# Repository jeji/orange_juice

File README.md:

# 我的频道 My Channel 
youtube: https://www.youtube.com/channel/UChTFW-Y9eg54AaTY_yama7A \
bilibili：https://b23.tv/pqzW2up

# 版本信息 Release Note
2022/10/09: v0.8 Reverse the polarity to match the common wire setup \
2022/02/06: v0.7 bate release version, passed function and stable test

**[香橙派Zero2版本](https://github.com/jeji/orange_juice_2)** \
**[Version for Orange Pi Zero2](https://github.com/jeji/orange_juice_2)** \

TODO:
- Integrate CAN controller/receivier
- Add motor driver socket as an universal socket for other feature, like: 
   - PWM controlled open loop buck convert for better fan noise 
   - Voron design MAX31865
   - Other SPI/UART/GPIO device

# 开始之前 Before You Start 
- 我并不是专业的电子工程师，设计本项目只是为了好玩和方便DIY Voron 3D打印机
- 你将自行承担由此带来的所有风险
- 社区有诸多反馈香橙派zero的CPU温度过高，所以在使用中请加强散热
- 本项目为基于GPL3.0的开源项目，欢迎魔改。如果你有更好的改进也请务必与我分享 
- **(!) 请特别注意文章中加粗和带"(!)"部分的内容**

- I'm not prefesstional electronic engineer, I designed this for fun and convenience while DIY my Voron printer
- You will take it as your own risk for any potential damages
- Overheat issue is being reported for OrangePi Zero H2+ CPU, hence a proper cooling fan even with cooling fin is strongly recommended
- This project is based GPL3.0 license, you are free to modify it to yourown version. Please do share the joy with me if you did that
- **(!) Please pay attention for the bold and with "(!)" content**

# 代号：橙汁 BoardName：Orange Juice

受全球芯片短缺情况影响，树莓派价格涨到了离谱的位置。
所以香橙派zero成了一个很好的替代品。120元左右的512MB版本可以满足做为klipper宿主的所有需求，甚至有点性能过剩。

klipper有诸多独特的功能需要使用到gpio针脚，每次都用排母端子去连接非常的不方便。在使用扩展板后不仅方便了许多，且可以得到额外的功能：
- 一个专为[ADXL345](https://www.adafruit.com/product/1231) 设计的接口将香橙派SPI1总线引出
- 一个专为[Adafruit MAX31865 board](https://www.adafruit.com/product/3328) 及其克隆版本设计的接口，作为软SPI使用了4个gpio接口
- 两个从香橙派引出的USB2.0 TypeA接口
- 一个UART接口
- 三组gpio控制的PWM输出接口，最大输出电压与输入电压相同
- 三组gpio接口配合5v电源接口，方便自定义其他功能
- 两组恒定5v输出接口
- 一个香橙派专用散热3010风扇安装位
- 自带降压电路，接受9~24V输入电压降压为5V供香橙派及其接口使用
- 扩展板大小及安装孔位与树莓派B系列保持一致
- 使用0805或更大尺寸封装贴片封装以方便手工贴片

Due to current chipset shortage sitatuion, raspberry pi price increase to an unreasonable level. 
Hence OrangePi Zero become a good alternative. A 25 dollars 512MB ram version meets all the requirments I need as a klipper host for my Voron V0.1, and actually even little bit over kill. 

Klipper has some advance features which need connect to gpio pins, it's not that convenience to use a pin header to connect gpio pin every time. Instead of that, with this board, it provides easier connection and more useful features:
- A dedicate [ADXL345](https://www.adafruit.com/product/1231) port is extended from OrangePi zero SPI1 bus
- A dedicate MAX31865 port connect to 4 gpio pins as a SW SPI connection, for [Adafruit MAX31865 board](https://www.adafruit.com/product/3328) or its clone
- Two USB2.0 Type A ports are extended from orange pi function pin
- A UART port for UART communication with printer MCU board
- Three klipper controllable pwm output ports, voltage depends on input DC voltage
- Three gpio port from orangepi with 5v power, for custom function
- Two 5v output ports
- A built-in 3010 chip cooling fan position
- A built-in step-down buck converter to convert DC 9~24v input to DC 5v to supply pi and 5v output socket
- Raspberry Pi B Serials board size and mount hole position compatible 
- 0805 or larger size SMD components are being used for hand soldering

# 如何使用 How to use
## 硬件 Hardware
PCB打板：[gerber文件](gerber/orange_juice_v0.8_gerber.zip)
- 你可以在嘉立创或者其他你喜欢的厂商免费打板
- 保持打板厂商默认设置即可

BOM：[电子元件BOM](bom/ibom.html)
- 在立创商城使用BOM单里lcsc part编号搜索即可找到对应原件型号
- 我使用的元件购买至淘宝，主要来自优信
- **(!) 香橙派针脚接头需要使用加高7.5mm的排母针脚，** 参考链接：[这里](https://item.taobao.com/item.htm?spm=a1z09.2.0.0.5abe2e8dp4SvIq&id=562698441144&_u=u181c59936e) 

PCB board：[gerber file](gerber/orange_juice_v0.8_gerber.zip)
- You can get the PCB board from JLC or other PCB manufactory 
- Usually, keep the defualt setting shall be ok when you place your order

BOM：[iBOM](bom/ibom.html)
- Search the component at [LCSC](https://lcsc.com/) via lcsc part number in the BOM
- I got my component from my trust taobao.com shop due to more reasble price 
- **(!) You need the famale pin head with 7.5mm extra feet height for orange pi,** reference link: [Here](https://item.taobao.com/item.htm?spm=a1z09.2.0.0.5abe2e8dp4SvIq&id=562698441144&_u=u181c59936e) 

## 软件 Software

请参考config目录下的orange_juice.cfg文件 \
orange_juice.cfg under config folder for you reference 

**(!) 以下配置依赖香橙派已经被正确配置成klipper客户端，并且香橙派配置名为"opi"** \
具体方法请参考 https://www.klipper3d.org/RPi_microcontroller.html \
**(!) Following configuration is assuming that your pi has been config as a klipper client already with name "opi"** \
If not, please refer to  https://www.klipper3d.org/RPi_microcontroller.html 

ADXL345配置 \
ADXL345 configuration 

```
[adxl345]
cs_pin: opi:gpio13
spi_bus: spidev1.0

[resonance_tester]
accel_chip: adxl345
probe_points: 60,60,20 #测试点，需要更改为你机器热床中心点，依次为x,y,z
```

MAX31865配置如下，**(!) 你还需要在本节或者其他文件里定义挤出机其他配置** \
MAX31865 config, **(!) you have to define other extruder value seperately** 

```
[extruder]
sensor_type: MAX31865
sensor_pin: opi:gpio1
spi_software_sclk_pin: opi:gpio2
spi_software_mosi_pin: opi:gpio0
spi_software_miso_pin: opi:gpio3
rtd_nominal_r: 100
rtd_reference_r: 430
rtd_num_of_wires: 2
rtd_use_50Hz_filter: True
```

PWM接口配置 \
PWM Port configuration

下为PWM控制的输出插座，对应插槽PWM1 ~ PWM3 \
**(!) 请注意，由于香橙派内核原因，PWM2和PWM3从系统加电启动到klipper正式运行前，默认为高电平，即为打开状态。待klipper正式运行后恢复设置状态** \
PWM control input-voltage output slot \
**(!) Pay attention, because of the linux kernel complied by Orange Pi, the PMW2 and PWM3 is on HIGH (ON) from the power on till klipper start functioning**
```
[fan_generic PWM1_Fan]
pin: opi:gpio10
max_power: 1
shutdown_speed: 0
cycle_time: 0.01
#hardware_pwm:
kick_start_time: 0.5
off_below: 0.1
#enable_pin:
#   See the "fan" section for a description of the above parameters.

[fan_generic PWM2_Fan]
pin: opi:gpio18
max_power: 1
shutdown_speed: 0
cycle_time: 0.01
#hardware_pwm:
kick_start_time: 0.5
off_below: 0.1
#enable_pin:
#   See the "fan" section for a description of the above parameters.

[fan_generic PWM3_Fan]
pin: opi:gpio19
max_power: 1
shutdown_speed: 0
cycle_time: 0.01
#hardware_pwm:
kick_start_time: 0.5
off_below: 0.1
#enable_pin:
#   See the "fan" section for a description of the above parameters.
```

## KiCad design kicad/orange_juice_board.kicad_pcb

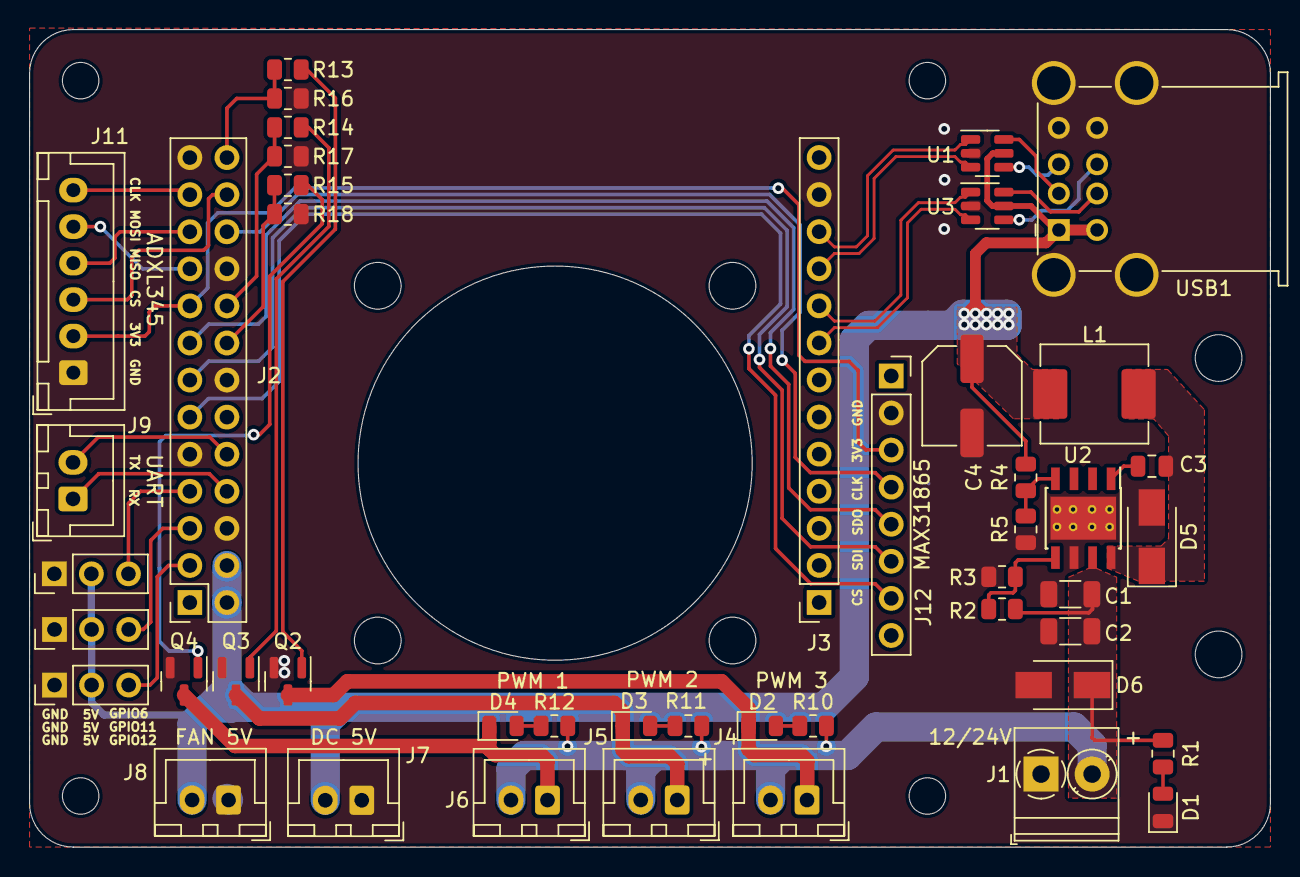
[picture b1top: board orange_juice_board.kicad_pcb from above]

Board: 2 copper layers, 85.0 x 56.0 mm, 52 parts (0 on the bottom side), 42 nets.

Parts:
C1, C2: 10uF; C_1206_3216Metric
C3: 10nF; C_0805_2012Metric
C4: 220uF; C_Elec_6.3x5.4
D2: PWM1_STATUS; LED_0805_2012Metric
D3, D3#2: PWM2_STATUS; LED_0805_2012Metric
D4: PWM3_STATUS; LED_0805_2012Metric
D5: B340A; D_SMA
D6: SMAJ24A; D_SMA
H5, H6, H7, H8: MH_FAN; MountingHole_3.2mm_M3
H9, H10: MH_MAX31865; MountingHole_3.2mm_M3
J2: DC_INPUT; TerminalBlock_Phoenix_PT-1,5-2-3.5-H_1x02_P3.50mm_Horizontal
J3: CONN_ADXL345; JST_XH_B6B-XH-A_1x06_P2.50mm_Vertical
J4: OrangePi Zero GPIO PINs; PinSocket_2x13_P2.54mm_Vertical
J7: OrangePi Zero Function Interface; PinSocket_1x13_P2.54mm_Vertical
J8: FAN_5v; JST_XH_B2B-XH-A_1x02_P2.50mm_Vertical
J9: PWR_5v; JST_XH_B2B-XH-A_1x02_P2.50mm_Vertical
J10: GPIO12_Head; PinHeader_1x03_P2.54mm_Vertical
J10#2: PWM_OUT1; JST_XH_B2B-XH-A_1x02_P2.50mm_Vertical
J11: CONN_UART; JST_XH_B2B-XH-A_1x02_P2.50mm_Vertical
J12: PWM_OUT2; JST_XH_B2B-XH-A_1x02_P2.50mm_Vertical
J12#2: Conn_01x08; PinSocket_1x08_P2.54mm_Vertical
J13: GPIO6_Head; PinHeader_1x03_P2.54mm_Vertical
J14: GPIO11_Head; PinHeader_1x03_P2.54mm_Vertical
J15: PWM_OUT3; JST_XH_B2B-XH-A_1x02_P2.50mm_Vertical
L1: 22uH; L_Abracon_ASPI-0630LR
Q2, Q3, Q4: AO3400A; SOT-23
R2: 100K; R_0805_2012Metric
R3: 25K5; R_0805_2012Metric
R4: 10K; R_0805_2012Metric
R4#2, R7, R7#2, R10: 4k7; R_0805_2012Metric
R5, R8, R14: 100; R_0805_2012Metric
R5#2: 3.24K; R_0805_2012Metric
R6, R9, R15: 10k; R_0805_2012Metric
U1, U3: USBLC6-2SC6; SOT-23-6
U2: TPS5430DDA; TI_SO-PowerPAD-8_ThermalVias
USB1: USB_A_Port_x2; USB_A_Wuerth_61400826021_Horizontal_Stacked

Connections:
BUCK_BOOT: C3.2, U2.1 (BOOT)
BUCK_EN: R2.2, R3.1, U2.5 (EN)
BUCK_IN: C1.1, C2.1, D6.1 (A1), J2.2, J10#2.2, J12.2, J15.2, R2.1, R4#2.2, R7.1, R7#2.2, R10.2, U2.7 (VIN)
BUCK_OUT: C4.1, J4.2, J4.4, J8.2, J9.2, J10.2, J13.2, J14.2, L1.2, R4.1, U1.5 (VBUS), U3.5 (VBUS), USB1.1 (VCC), USB1.5 (VCC)
BUCK_PH: C3.1, D5.1 (K), L1.1, U2.8 (PH)
BUCK_VSNS: R4.2, R5#2.1, U2.4 (VSENSE)
GND: C1.2, C2.2, C4.2, D3#2.1 (K), D5.2 (A), D6.2 (A2), J2.1, J3.1, J4.6, J4.9, J4.14, J4.20, J4.25, J7.12, J8.1, J9.1, J10.1, J12#2.2, J13.1, J14.1, Q2.2 (S), Q3.2 (S), Q4.2 (S), R3.2, R5#2.2, R6.1, R9.1, R15.1, U1.2 (GND), U2.6 (GND), U2.9 (GNDPAD), U3.2 (GND), USB1.4 (GND), USB1.8 (GND), USB1.9 (Shield)
GPIO6: J4.7, J13.3
GPIO11: J4.5, J14.3
GPIO12: J4.3, J10.3
GPIO_0_SDI: J4.13, J12#2.6
GPIO_1_CS: J4.11, J12#2.7
GPIO_2_CLK: J4.22, J12#2.4
GPIO_3_SDO: J4.15, J12#2.5
GPIO_10: J4.26, R5.2, R6.2
GPIO_18: J4.18, R8.2, R9.2
GPIO_19: J4.16, R14.2, R15.2
unnamed: D3#2.2 (A), R7.2
unnamed: D2.1 (K), J10#2.1, Q2.3 (D)
unnamed: D2.2 (A), R4#2.1
unnamed: D3.1 (K), J12.1, Q3.3 (D)
unnamed: D3.2 (A), R7#2.1
unnamed: D4.1 (K), J15.1, Q4.3 (D)
unnamed: D4.2 (A), R10.1
unnamed: Q2.1 (G), R5.1
unnamed: Q3.1 (G), R8.1
unnamed: Q4.1 (G), R14.1
PI_3.3V: J3.2, J4.17, J12#2.3
SPI1_CLK: J3.6, J4.23
SPI1_CS: J3.3, J4.24
SPI1_MISO: J3.4, J4.21
SPI1_MOSI: J3.5, J4.19
UART1_RX: J4.10, J11.2
UART1_TX: J4.8, J11.1
USB2_Conn_D+: U1.4 (I/O2), USB1.3 (D+)
USB2_Conn_D-: U1.6 (I/O1), USB1.2 (D-)
USB2_D+: J7.10, U1.3 (I/O2)
USB2_D-: J7.11, U1.1 (I/O1)
USB3_Conn_D+: U3.4 (I/O2), USB1.7 (D+)
USB3_Conn_D-: U3.6 (I/O1), USB1.6 (D-)
USB3_D+: J7.8, U3.3 (I/O2)
USB3_D-: J7.9, U3.1 (I/O1)

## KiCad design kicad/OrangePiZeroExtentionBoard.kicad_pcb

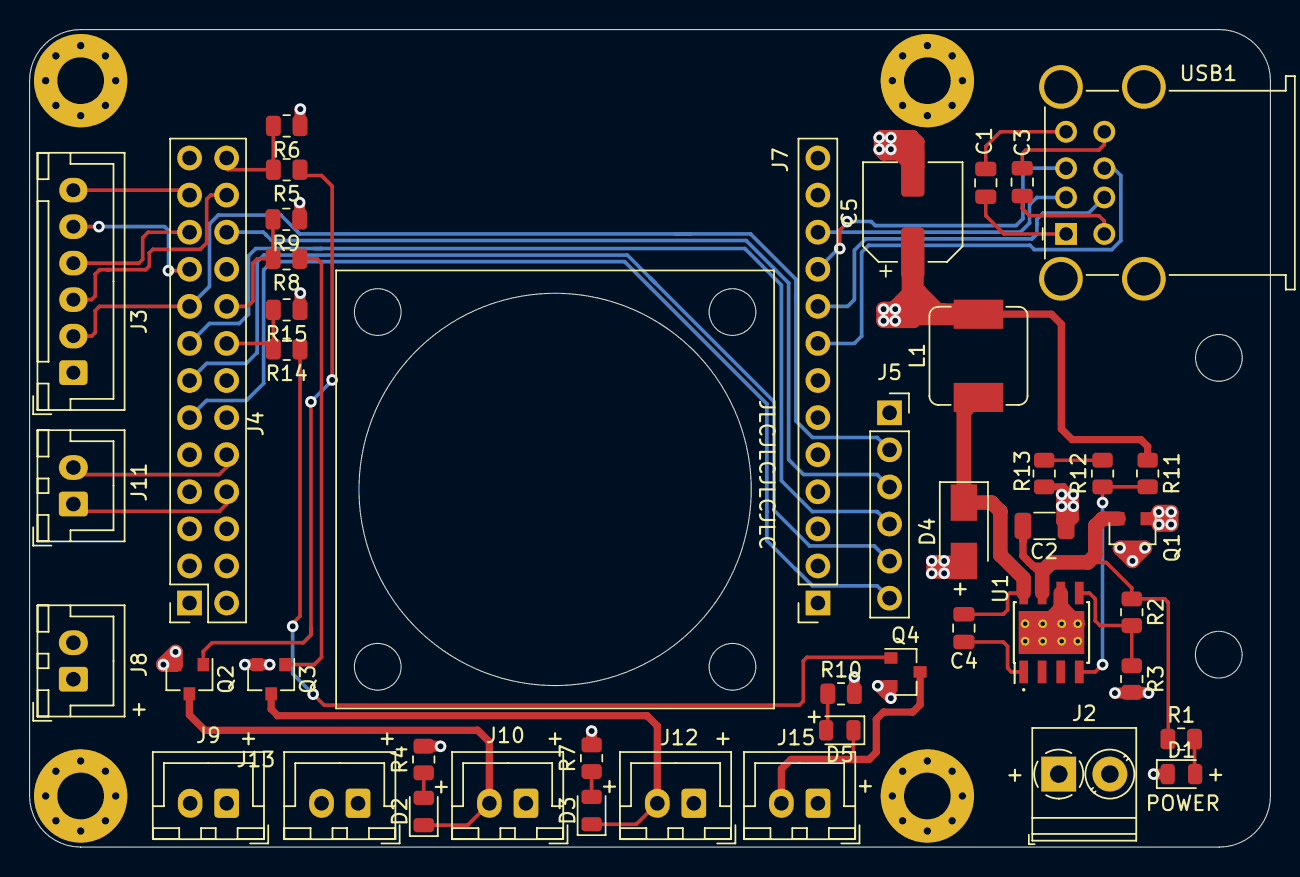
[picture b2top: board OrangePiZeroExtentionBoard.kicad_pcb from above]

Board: 4 copper layers, 85.0 x 56.0 mm, 54 parts (0 on the bottom side), 37 nets.

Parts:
C1, C3: 22u; C_0805_2012Metric
C2: 10u; C_1206_3216Metric
C4: 10n; C_0805_2012Metric
C5: 220u; CP_Elec_6.3x5.4
D1: PWR_LED; LED_0805_2012Metric
D2: PWM1_STATUS; LED_0805_2012Metric
D3: PWM2_STATUS; LED_0805_2012Metric
D4: B340A; D_SMA
D5: PWM3_STATUS; LED_0805_2012Metric
H1, H2, H3, H4: MH_Board; MountingHole_3.2mm_M3_Pad_Via
H5, H6, H7, H8: MH_FAN; MountingHole_3.2mm_M3
H9, H10: MH_MAX31865; MountingHole_3.2mm_M3
J2: DC_INPUT; TerminalBlock_Phoenix_PT-1,5-2-3.5-H_1x02_P3.50mm_Horizontal
J3: CONN_ADXL345; JST_XH_B6B-XH-A_1x06_P2.50mm_Vertical
J4: OrangePi Zero GPIO PINs; PinSocket_2x13_P2.54mm_Vertical
J5: Conn_MAX31865; PinSocket_1x06_P2.54mm_Vertical
J7: OrangePi Zero Function Interface; PinSocket_1x13_P2.54mm_Vertical
J8: FAN_5v; JST_XH_B2B-XH-A_1x02_P2.50mm_Vertical
J9: PWR_5v; JST_XH_B2B-XH-A_1x02_P2.50mm_Vertical
J10: PWM_OUT1; JST_XH_B2B-XH-A_1x02_P2.50mm_Vertical
J11: CONN_UART; JST_XH_B2B-XH-A_1x02_P2.50mm_Vertical
J12: PWM_OUT2; JST_XH_B2B-XH-A_1x02_P2.50mm_Vertical
J13: FAN_12/24v; JST_XH_B2B-XH-A_1x02_P2.50mm_Vertical
J15: PWM_OUT3; JST_XH_B2B-XH-A_1x02_P2.50mm_Vertical
L1: 15u; L_Sumida_CDMC6D28_7.25x6.5mm
Q1: AO3401A; SOT-23
Q2, Q3, Q4: AO3400A; SOT-23
R1, R4, R7, R10: 4k7; R_0805_2012Metric
R2: 100k; R_0805_2012Metric
R3: 21k; R_0805_2012Metric
R5, R8, R14: 100; R_0805_2012Metric
R6, R9, R11, R15: 10k; R_0805_2012Metric
R12: 3k; R_0805_2012Metric
R13: 240; R_0805_2012Metric
U1: TPS5430; TI_SO-PowerPAD-8_ThermalVias
USB1: USB_A_Port_x2; USB_A_Wuerth_61400826021_Horizontal_Stacked

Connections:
+3V3: J3.2, J4.17, J5.2
+5V: C1.1, C3.1, C5.1, J4.2, J4.4, J7.13, J8.1, J9.1, L1.2, R11.1, USB1.1, USB1.5
BUCK_BOOT: C4.1, U1.1
BUCK_EN: R2.2, R3.1, U1.5
BUCK_IN: C2.1, Q1.2, R1.1, R2.1, U1.7
BUCK_PH: C4.2, D4.1, L1.1, U1.8
BUCK_VSNS: R11.2, R12.1, U1.4
DCIN: J2.1, J10.1, J12.1, J13.1, J15.1, Q1.3, R4.2, R7.2, R10.2
GND: C1.2, C2.2, C3.2, C5.2, D1.1, D4.2, J2.2, J3.1, J4.6, J4.9, J4.14, J4.20, J4.25, J5.1, J7.12, J8.2, J9.2, J13.2, Q1.1, Q2.2, Q3.2, Q4.2, R3.2, R6.1, R9.1, R13.2, R15.1, U1.6, U1.9, USB1.4, USB1.8
GPIO_0_SDI: J4.13, J5.5
GPIO_1_CS: J4.11, J5.6
GPIO_2_CLK: J4.22, J5.3
GPIO_3_SDO: J4.15, J5.4
GPIO_10: J4.26, R5.2, R6.2
GPIO_18: J4.18, R8.2, R9.2
GPIO_19: J4.16, R14.2, R15.2
unnamed: D1.2, R1.2
unnamed: D2.1, J10.2, Q2.3
unnamed: D2.2, R4.1
unnamed: D3.1, J12.2, Q3.3
unnamed: D3.2, R7.1
unnamed: D5.1, J15.2, Q4.3
unnamed: D5.2, R10.1
unnamed: Q2.1, R5.1
unnamed: Q3.1, R8.1
unnamed: Q4.1, R14.1
unnamed: R12.2, R13.1
SPI1_CLK: J3.6, J4.23
SPI1_CS: J3.3, J4.24
SPI1_MISO: J3.4, J4.21
SPI1_MOSI: J3.5, J4.19
UART1_RX: J4.8, J11.1
UART1_TX: J4.10, J11.2
USB_DM2: J7.11, USB1.2
USB_DM3: J7.9, USB1.6
USB_DP2: J7.10, USB1.3
USB_DP3: J7.8, USB1.7

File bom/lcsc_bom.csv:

Reference, Quantity, Value, Footprint, LCSC Part #
C1 C3 ,2,22u,Capacitor_SMD:C_0805_2012Metric,C29277
C2 ,1,10u,Capacitor_SMD:C_1206_3216Metric,C13585
C4 ,1,10n,Capacitor_SMD:C_0805_2012Metric,C519911
C5 ,1,220u,Capacitor_SMD:CP_Elec_6.3x5.4,C3345
D1 ,1,PWR_LED,LED_SMD:LED_0805_2012Metric,C84260
D2 ,1,PWM1_STATUS,LED_SMD:LED_0805_2012Metric,C84260
D3 ,1,PWM2_STATUS,LED_SMD:LED_0805_2012Metric,C84260
D4 ,1,B340A,Diode_SMD:D_SMA,C64982
D5 ,1,PWM3_STATUS,LED_SMD:LED_0805_2012Metric,C84260
H1 H2 H3 H4 ,4,MH_Board,MountingHole:MountingHole_3.2mm_M3_Pad_Via,
H5 H6 H7 H8 ,4,MH_FAN,MountingHole:MountingHole_3.2mm_M3,
H9 H10 ,2,MH_MAX31865,MountingHole:MountingHole_3.2mm_M3,
J10 ,1,PWM_OUT1,Connector_JST:JST_XH_B2B-XH-A_1x02_P2.50mm_Vertical,C158012
J11 ,1,CONN_UART,Connector_JST:JST_XH_B2B-XH-A_1x02_P2.50mm_Vertical,C158012
J12 ,1,PWM_OUT2,Connector_JST:JST_XH_B2B-XH-A_1x02_P2.50mm_Vertical,C158012
J13 ,1,FAN_12/24v,Connector_JST:JST_XH_B2B-XH-A_1x02_P2.50mm_Vertical,C158012
J15 ,1,PWM_OUT3,Connector_JST:JST_XH_B2B-XH-A_1x02_P2.50mm_Vertical,C158012
J2 ,1,DC_INPUT,"TerminalBlock_Phoenix:TerminalBlock_Phoenix_PT-1,5-2-3.5-H_1x02_P3.50mm_Horizontal",C784942
J3 ,1,CONN_ADXL345,Connector_JST:JST_XH_B6B-XH-A_1x06_P2.50mm_Vertical,C144397
J4 ,1,OrangePi Zero GPIO PINs,Connector_PinSocket_2.54mm:PinSocket_2x13_P2.54mm_Vertical,
J5 ,1,Conn_MAX31865,Connector_PinSocket_2.54mm:PinSocket_1x06_P2.54mm_Vertical,C40877
J7 ,1,OrangePi Zero Function Interface,Connector_PinSocket_2.54mm:PinSocket_1x13_P2.54mm_Vertical,
J8 ,1,FAN_5v,Connector_JST:JST_XH_B2B-XH-A_1x02_P2.50mm_Vertical,C158012
J9 ,1,PWR_5v,Connector_JST:JST_XH_B2B-XH-A_1x02_P2.50mm_Vertical,C158012
L1 ,1,15u,Inductor_SMD:L_Sumida_CDMC6D28_7.25x6.5mm,C718391
Q1 ,1,AO3401A,Package_TO_SOT_SMD:SOT-23,C306862
Q2 Q3 Q4 ,3,AO3400A,Package_TO_SOT_SMD:SOT-23,C700953
R6 R9 R11 R15 ,4,10k,Resistor_SMD:R_0805_2012Metric,C84376
R12 ,1,3k,Resistor_SMD:R_0805_2012Metric,C126350
R13 ,1,240,Resistor_SMD:R_0805_2012Metric,C185292
R2 ,1,100k,Resistor_SMD:R_0805_2012Metric,C96346
R3 ,1,21k,Resistor_SMD:R_0805_2012Metric,C137569
R1 R4 R7 R10 ,4,4k7,Resistor_SMD:R_0805_2012Metric,C60816
R5 R8 R14 ,3,100,Resistor_SMD:R_0805_2012Metric,C105577
U1 ,1,TPS5430,Package_SO:TI_SO-PowerPAD-8_ThermalVias,C9864
USB1 ,1,USB_A_Port_x2,Connector_USB:USB_A_Wuerth_61400826021_Horizontal_Stacked,C12049

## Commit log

2021-12-28 initial upload
2021-12-28 initial version
2021-12-28 update description
2021-12-28 update pin head footprint
2021-12-28 update images
2022-01-01 update bom
2022-01-02 update details
2022-01-04 update readme chinese
2022-01-04 update kicad files
2022-01-05 update gerber
2022-01-09 version 0.3
2022-01-16 bate version
2022-01-17 add ignore
2022-01-30 Official v0.6 release
2022-01-30 update v0.6 readme
2022-02-06 minor update
2022-02-06 I don't know what's updated...
2022-02-06 update folder
2022-02-06 rename
2022-10-09 Update readme and config
    Update readme with sw config example
2022-10-09 Reverse polarity
2022-10-09 v0.8 Update
    reverse the polarity
2022-10-15 Update front silk text
2022-10-17 Update front silk symbol
    Correct the power socket symbol
